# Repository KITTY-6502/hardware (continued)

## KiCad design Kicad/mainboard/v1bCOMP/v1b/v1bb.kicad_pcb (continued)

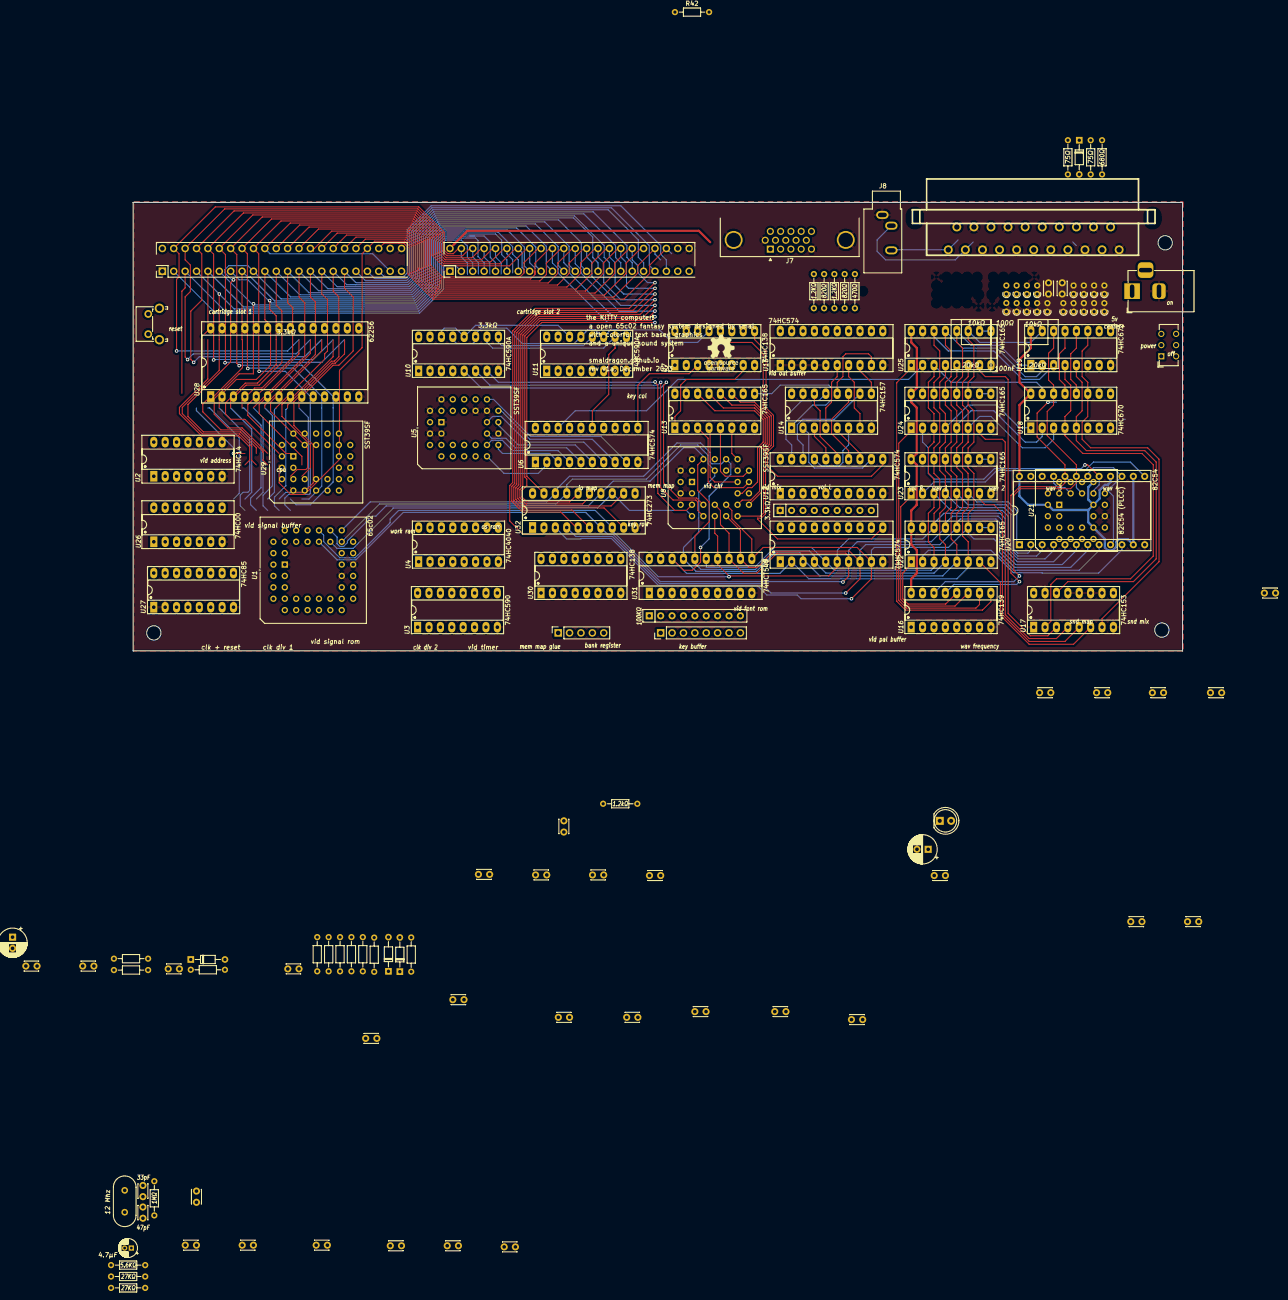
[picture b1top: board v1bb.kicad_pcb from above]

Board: 2 copper layers, 234.0 x 100.0 mm, 134 parts (0 on the bottom side), 193 nets.

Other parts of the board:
C6, C7: C_Polarized; CP_Radial_D6.3mm_P2.50mm
D2: D_Small; D_DO-34_SOD68_P7.62mm_Horizontal
D3: Power; LED_D5.0mm
J3: Barrel_Jack_MountingPin; BarrelJack_Horizontal
J4: SCART-F; SCART
J5, J6: Conn_02x22_Odd_Even; EdgeHeader_2x22_P2.54mm_Vertical
J7: DE15_Plug_HighDensity_MountingHoles; DSUB-15-HD_Female_Horizontal_P2.29x1.98mm_EdgePinOffset3.03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
J8: AudioJack3; Jack_3.5mm_CUI_SJ1-3533NG_Horizontal
R38, R40: 75Ω; R_Axial_DIN0204_L3.6mm_D1.6mm_P7.62mm_Horizontal
R39: 1.2kΩ; R_Axial_DIN0204_L3.6mm_D1.6mm_P7.62mm_Horizontal
R41: 680Ω; R_Axial_DIN0204_L3.6mm_D1.6mm_P7.62mm_Horizontal
SW2: SW_DPDT_x2; SW_CuK_JS202011AQN_DPDT_Angled

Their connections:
3M: J5.36, J6.36; also elsewhere on the board
+5V: C6.1, C7.1, J5.2, J6.2, R38.1, R41.1, SW2.2 (B), SW2.5 (B); also elsewhere on the board
A0: J5.33, J6.33; also elsewhere on the board
A1: J5.31, J6.31; also elsewhere on the board
A2: J5.29, J6.29; also elsewhere on the board
A3: J5.27, J6.27; also elsewhere on the board
A4: J5.25, J6.25; also elsewhere on the board
A5: J5.23, J6.23; also elsewhere on the board
A6: J5.21, J6.21; also elsewhere on the board
A7: J5.19, J6.19; also elsewhere on the board
A8: J5.17, J6.17; also elsewhere on the board
A9: J5.15, J6.15; also elsewhere on the board
A10: J5.13, J6.13; also elsewhere on the board
A11: J5.11, J6.11; also elsewhere on the board
A12: J5.9, J6.9; also elsewhere on the board
A13: J5.7, J6.7; also elsewhere on the board
A14: J5.5, J6.5; also elsewhere on the board
A15: J5.3, J6.3; also elsewhere on the board
B0: J5.34, J6.34; also elsewhere on the board
B1: J5.32, J6.32; also elsewhere on the board
B2: J5.30, J6.30; also elsewhere on the board
B3: J5.28, J6.28; also elsewhere on the board
B4: J5.26, J6.26; also elsewhere on the board
B5: J5.24, J6.24; also elsewhere on the board
B6: J5.22, J6.22; also elsewhere on the board
B7: J5.20, J5.41, J6.20; also elsewhere on the board
D0: J5.18, J6.18; also elsewhere on the board
D1: J5.16, J6.16; also elsewhere on the board
D2: J5.14, J6.14; also elsewhere on the board
D3: J5.12, J6.12; also elsewhere on the board
D4: J5.10, J6.10; also elsewhere on the board
D5: J5.8, J6.8; also elsewhere on the board
D6: J5.6, J6.6; also elsewhere on the board
D7: J5.4, J6.4; also elsewhere on the board
GND: C6.2, C7.2, D3.1 (K), J3.2, J4.4, J4.5, J4.8, J4.9, J4.13, J4.17, J4.18, J4.21, J5.1, J5.44, J6.1, J6.44, J7.0, J7.5, J7.6, J7.7, J7.8, J7.9, J7.10, J8.S, R40.2; also elsewhere on the board
LEFT: J4.3, J8.T; also elsewhere on the board
unnamed: D2.2 (A), R38.2
unnamed: D2.1 (K), J4.16, R40.1
unnamed: D3.2 (A), R41.2
unnamed: J4.19, R39.2
RIGHT: J4.1, J8.R; also elsewhere on the board
ROM DISABLE: J5.42; also elsewhere on the board
R/~W: J5.40, J6.40; also elsewhere on the board
VBUS: J3.1, SW2.3 (C), SW2.6 (C)
VBlue: J4.7, J7.3; also elsewhere on the board
VGreen: J4.11, J7.2; also elsewhere on the board
VRed: J4.15, J7.1; also elsewhere on the board
~B7: J6.41; also elsewhere on the board
~CART: J5.35, J6.35; also elsewhere on the board
~HSync: J7.13; also elsewhere on the board
~NMI: J5.37, J6.37; also elsewhere on the board
~RESET: J5.39, J6.39; also elsewhere on the board
~R/W: J5.38, J6.38; also elsewhere on the board
~Sync: R39.1; also elsewhere on the board
~VSync: J7.14; also elsewhere on the board
